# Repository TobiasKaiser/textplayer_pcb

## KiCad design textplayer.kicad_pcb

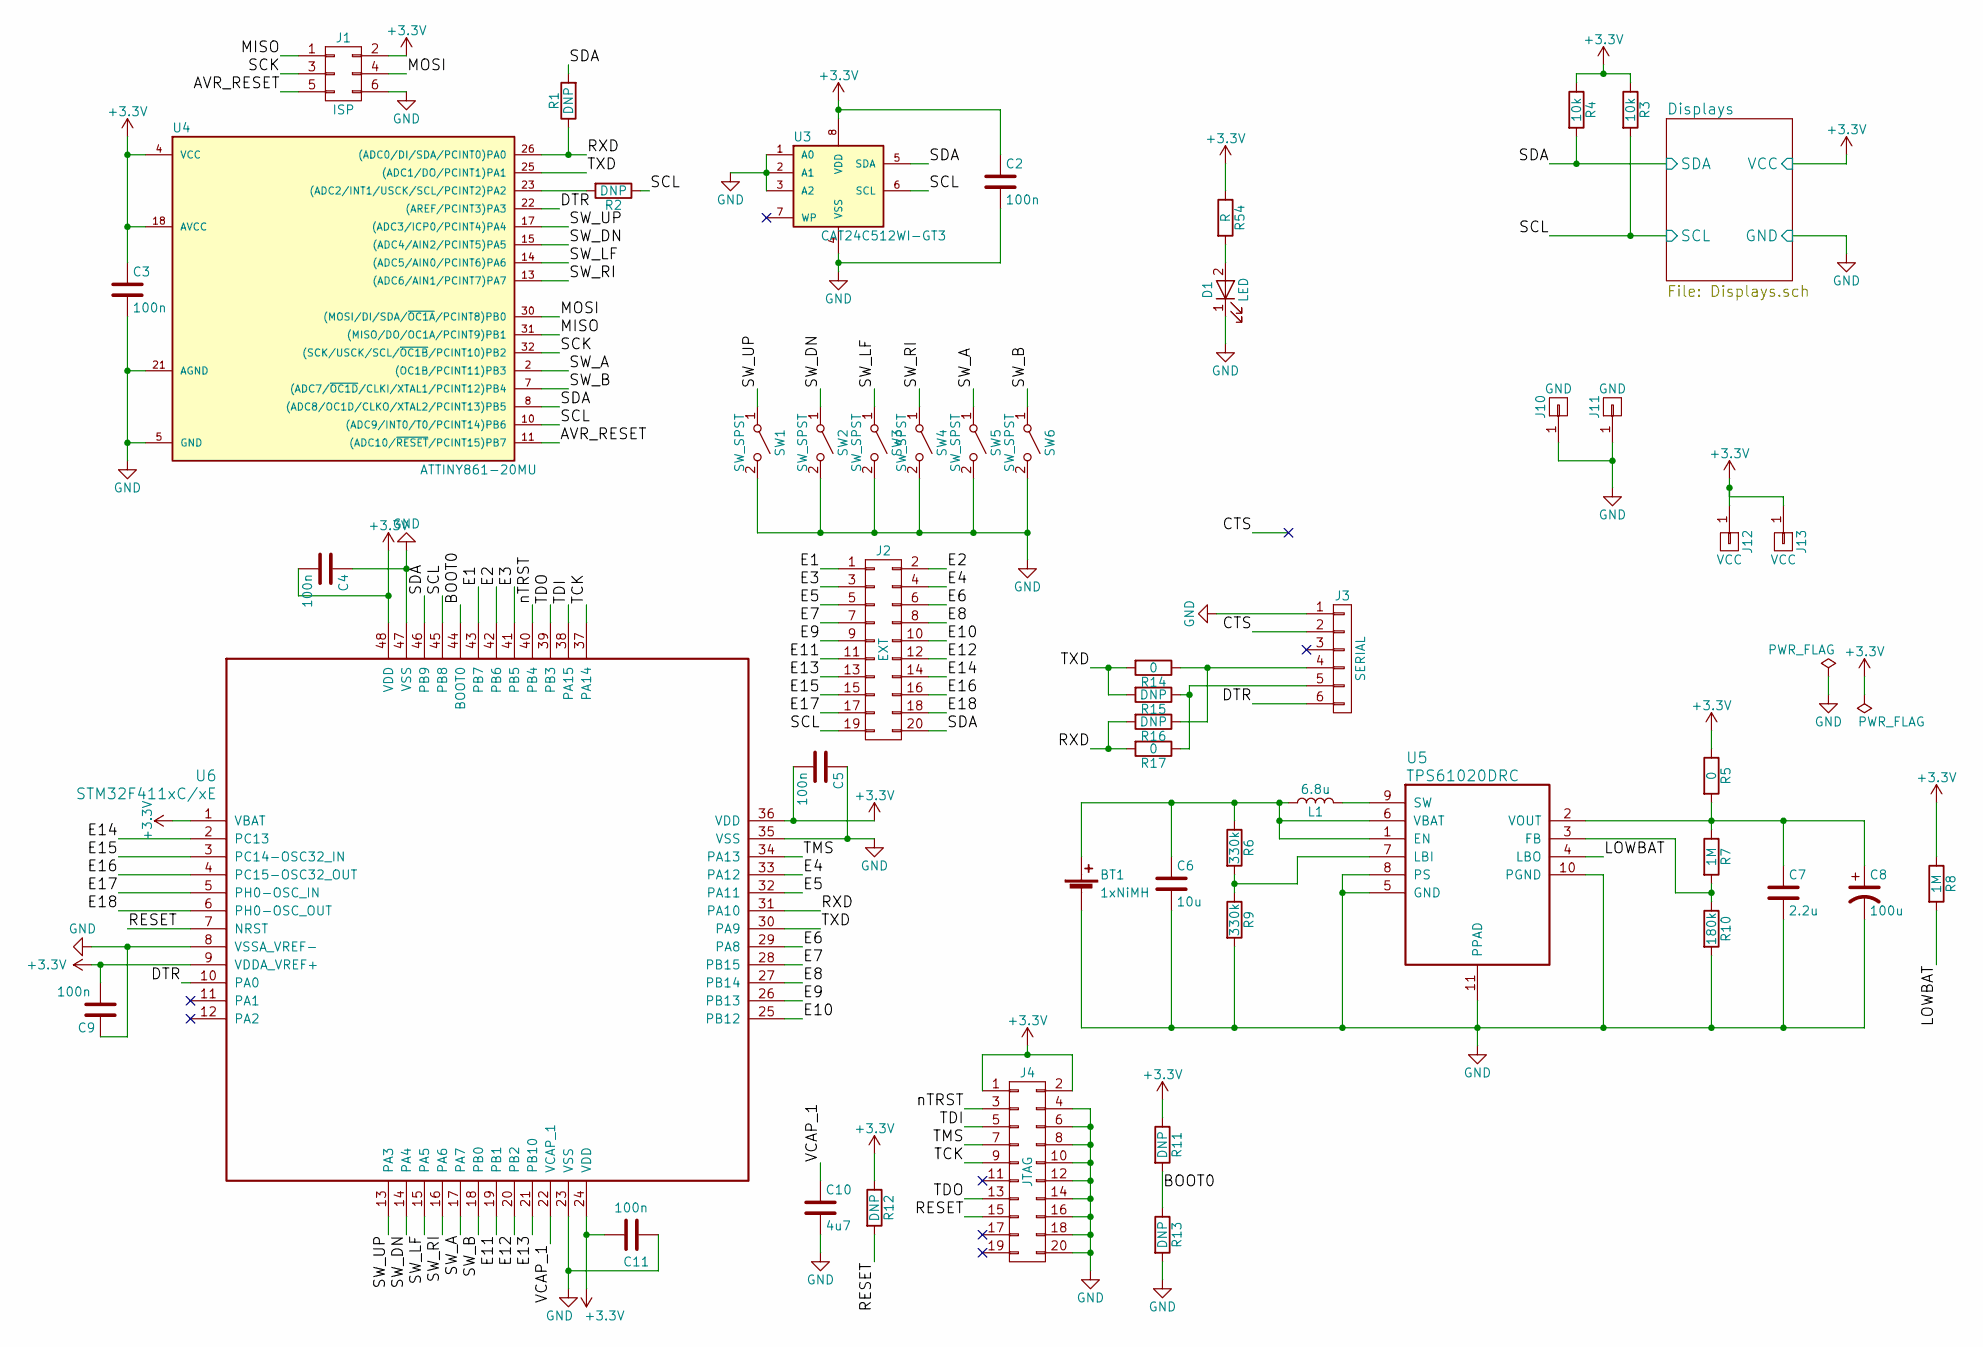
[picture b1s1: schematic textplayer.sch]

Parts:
BT1: 1xNiMH; BCAAPC
C2, C3, C4, C5, C9, C11: 100n; C_0805_HandSoldering
C6: 10u; C_0805_HandSoldering
C7: 2.2u; C_0805_HandSoldering
C8: 100u; CP_Tantalum_Case-B_EIA-3528-21_Hand
C10: 4u7; C_0805_HandSoldering
D1: LED; LED_0805
J1: ISP; Pin_Header_Straight_2x03_Pitch2.54mm
J2: EXT; Pin_Header_Straight_2x10_Pitch2.54mm
J3: SERIAL; Pin_Header_Straight_1x06_Pitch2.54mm
J4: JTAG; Pin_Header_Straight_2x10_Pitch2.54mm
J10: GND; Measurement_Point_Round-TH_Small
J11: GND; Measurement_Point_Round-SMD-Pad_Big
J12: VCC; Measurement_Point_Round-TH_Small
J13: VCC; Measurement_Point_Round-SMD-Pad_Big
L1: 6.8u; Inductor_B82462G4
R1, R2, R11, R12, R13, R15, R16: DNP; R_0805_HandSoldering
R3, R4: 10k; R_0805_HandSoldering
R5, R14, R17: 0; R_0805_HandSoldering
R6, R9: 330k; R_0805_HandSoldering
R7, R8: 1M; R_0805_HandSoldering
R10: 180k; R_0805_HandSoldering
R54: R; R_0805_HandSoldering
SW1, SW2, SW3, SW4, SW5, SW6: SW_SPST; SW_SPST_B3S-1000
U3: CAT24C512WI-GT3; TSSOP-8_4.4x3mm_Pitch0.65mm
U4: ATTINY861-20MU; QFN-32-1EP_5x5mm_Pitch0.5mm
U5: TPS61020DRC; S-PVSON-N10
U6: STM32F411xC/xE; QFN-48-1EP_7x7mm_Pitch0.5mm

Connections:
+3V3: C2.1, C3.1, C4.2, C5.2, C9.2, C11.2, J1.2, J4.1, J4.2, J12.1, J13.1, R3.1, R4.1, R5.1, R8.1, R11.1, R12.1, R54.1, U3.8 (VDD), U4.4 (VCC), U4.18 (AVCC), U6.1 (VBAT), U6.9 (VDDA_VREF+), U6.24 (VDD), U6.36 (VDD), U6.48 (VDD); also elsewhere on the board
/AVR_RESET: J1.5, U4.11 ((ADC10/~RESET~/PCINT15)PB7)
/BOOT0: R11.2, R13.1, U6.44 (BOOT0)
/CTS: J3.2
/DTR: J3.6, U4.22 ((AREF/PCINT3)PA3), U6.10 (PA0)
/E1: J2.1, U6.43 (PB7)
/E2: J2.2, U6.42 (PB6)
/E3: J2.3, U6.41 (PB5)
/E4: J2.4, U6.33 (PA12)
/E5: J2.5, U6.32 (PA11)
/E6: J2.6, U6.29 (PA8)
/E7: J2.7, U6.28 (PB15)
/E8: J2.8, U6.27 (PB14)
/E9: J2.9, U6.26 (PB13)
/E10: J2.10, U6.25 (PB12)
/E11: J2.11, U6.19 (PB1)
/E12: J2.12, U6.20 (PB2)
/E13: J2.13, U6.21 (PB10)
/E14: J2.14, U6.2 (PC13)
/E15: J2.15, U6.3 (PC14-OSC32_IN)
/E16: J2.16, U6.4 (PC15-OSC32_OUT)
/E17: J2.17, U6.5 (PH0-OSC_IN)
/E18: J2.18, U6.6 (PH0-OSC_OUT)
/LOWBAT: R8.2, U5.4 (LBO)
/MISO: J1.1, U4.31 ((MISO/DO/OC1A/PCINT9)PB1)
/MOSI: J1.4, U4.30 ((MOSI/DI/SDA/~OC1A~/PCINT8)PB0)
/RESET: J4.15, R12.2, U6.7 (NRST)
/RXD: R1.1, R16.2, R17.2, U4.26 ((ADC0/DI/SDA/PCINT0)PA0), U6.31 (PA10)
/SCK: J1.3, U4.32 ((SCK/USCK/SCL/~OC1B~/PCINT10)PB2)
/SCL: J2.19, R2.1, R3.2, U3.6 (SCL), U4.10 ((ADC9/INT0/T0/PCINT14)PB6), U6.45 (PB8); also elsewhere on the board
/SDA: J2.20, R1.2, R4.2, U3.5 (SDA), U4.8 ((ADC8/OC1D/CLKO/XTAL2/PCINT13)PB5), U6.46 (PB9); also elsewhere on the board
/SW_A: SW5.1 (A), U4.2 ((OC1B/PCINT11)PB3), U6.17 (PA7)
/SW_B: SW6.1 (A), U4.7 ((ADC7/~OC1D~/CLKI/XTAL1/PCINT12)PB4), U6.18 (PB0)
/SW_DN: SW2.1 (A), U4.15 ((ADC4/AIN2/PCINT5)PA5), U6.14 (PA4)
/SW_LF: SW3.1 (A), U4.14 ((ADC5/AIN0/PCINT6)PA6), U6.15 (PA5)
/SW_RI: SW4.1 (A), U4.13 ((ADC6/AIN1/PCINT7)PA7), U6.16 (PA6)
/SW_UP: SW1.1 (A), U4.17 ((ADC3/ICP0/PCINT4)PA4), U6.13 (PA3)
/TCK: J4.9, U6.37 (PA14)
/TDI: J4.5, U6.38 (PA15)
/TDO: J4.13, U6.39 (PB3)
/TMS: J4.7, U6.34 (PA13)
/TXD: R14.2, R15.2, U4.25 ((ADC1/DO/PCINT1)PA1), U6.30 (PA9)
/VCAP_1: C10.1, U6.22 (VCAP_1)
/nTRST: J4.3, U6.40 (PB4)
GND: BT1.2 (-), C2.2, C3.2, C4.1, C5.1, C6.2, C7.2, C8.2, C9.1, C10.2, C11.1, D1.1 (K), J1.6, J3.1, J4.4, J4.6, J4.8, J4.10, J4.12, J4.14, J4.16, J4.18, J4.20, J10.1, J11.1, R9.2, R10.2, R13.2, SW1.2 (B), SW2.2 (B), SW3.2 (B), SW4.2 (B), SW5.2 (B), SW6.2 (B), U3.1 (A0), U3.2 (A1), U3.3 (A2), U3.4 (VSS), U4.5 (GND), U4.21 (AGND), U5.5 (GND), U5.8 (PS), U5.10 (PGND), U5.11 (PPAD), U6.8 (VSSA_VREF-), U6.23 (VSS), U6.35 (VSS), U6.47 (VSS); also elsewhere on the board
unnamed: BT1.1 (+), C6.1, L1.1, R6.1, U5.1 (EN), U5.6 (VBAT)
unnamed: C7.1, C8.1, R5.2, R7.1, U5.2 (VOUT)
unnamed: D1.2 (A), R54.2
unnamed: J3.4, R14.1, R16.1
unnamed: J3.5, R15.1, R17.1
unnamed: L1.2, U5.9 (SW)
unnamed: R2.2, U4.23 ((ADC2/INT1/USCK/SCL/PCINT2)PA2)
unnamed: R6.2, R9.1, U5.7 (LBI)
unnamed: R7.2, R10.1, U5.3 (FB)

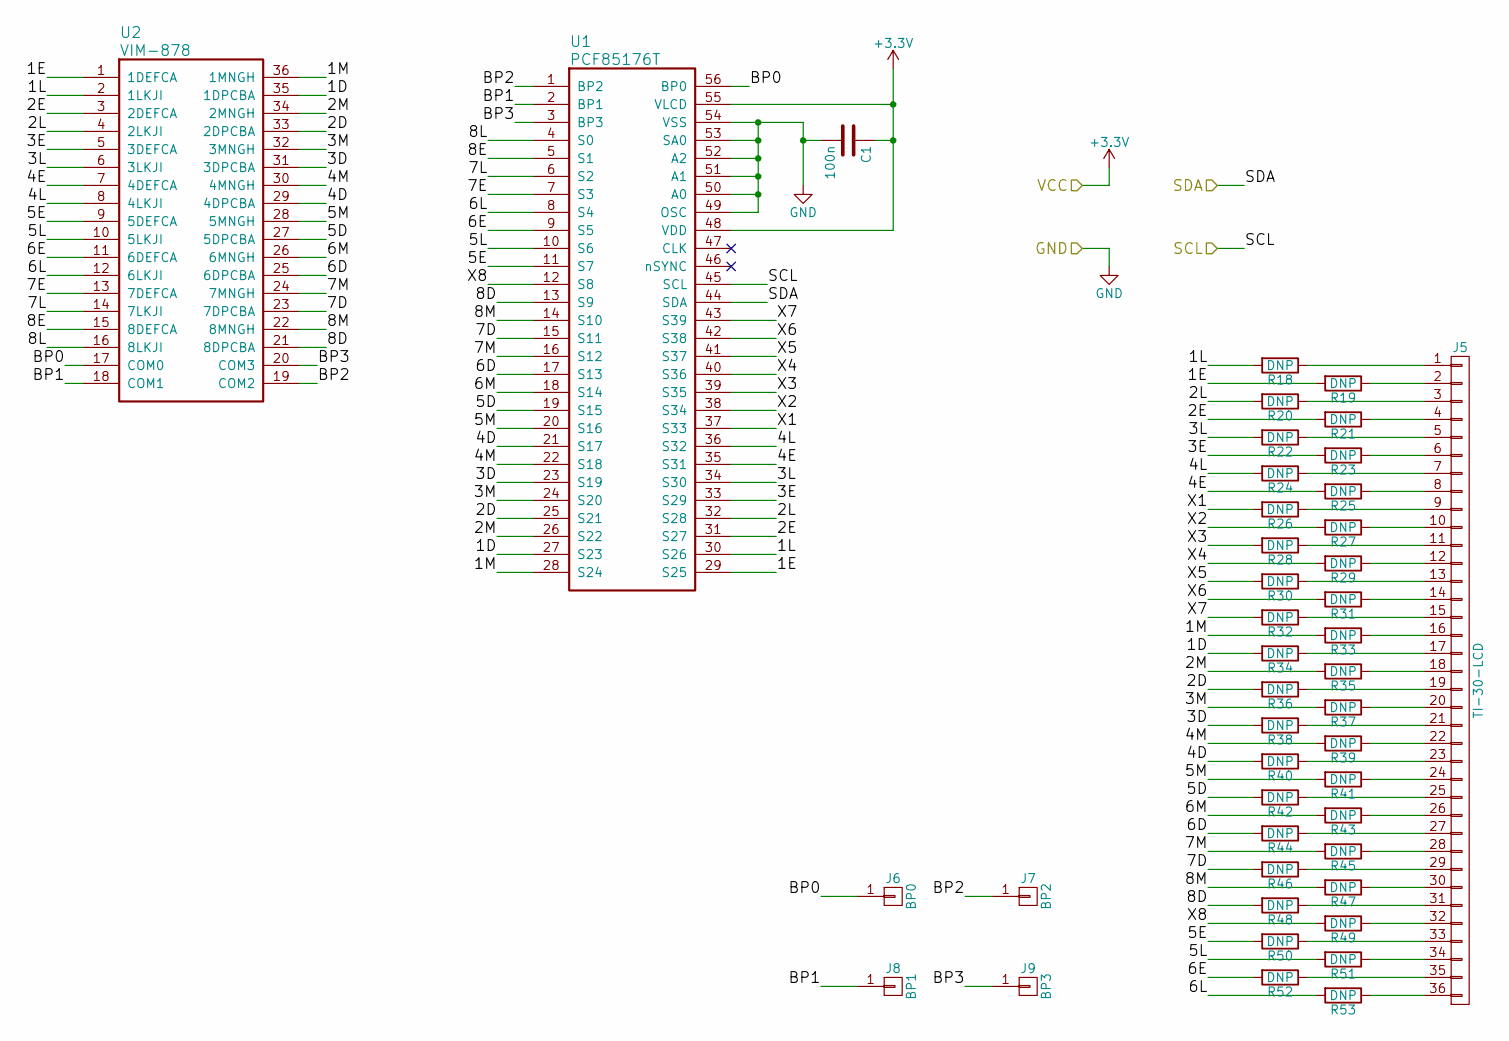
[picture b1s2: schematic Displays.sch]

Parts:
C1: 100n; C_0805_HandSoldering
J5: TI-30-LCD
J6: BP0; Measurement_Point_Square-SMD-Pad_Small
J7: BP2; Measurement_Point_Square-SMD-Pad_Small
J8: BP1; Measurement_Point_Square-SMD-Pad_Small
J9: BP3; Measurement_Point_Square-SMD-Pad_Small
R18, R19, R20, R21, R22, R23, R24, R25, R26, R27, R28, R29, R30, R31, R32, R33, R34, R35, R36, R37, R38, R39, R40, R41, R42, R43, R44, R45, R46, R47, R48, R49, R50, R51, R52, R53: DNP; R_0805_HandSoldering
U1: PCF85176T; TSSOP-56_6.1x14mm_Pitch0.5mm
U2: VIM-878

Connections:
+3V3: C1.1, U1.48 (VDD), U1.55 (VLCD); also elsewhere on the board
/Displays/1D: R34.2, U1.27 (S23), U2.35 (1DPCBA)
/Displays/1E: R19.2, U1.29 (S25), U2.1 (1DEFCA)
/Displays/1L: R18.2, U1.30 (S26), U2.2 (1LKJI)
/Displays/1M: R33.2, U1.28 (S24), U2.36 (1MNGH)
/Displays/2D: R36.2, U1.25 (S21), U2.33 (2DPCBA)
/Displays/2E: R21.2, U1.31 (S27), U2.3 (2DEFCA)
/Displays/2L: R20.2, U1.32 (S28), U2.4 (2LKJI)
/Displays/2M: R35.2, U1.26 (S22), U2.34 (2MNGH)
/Displays/3D: R38.2, U1.23 (S19), U2.31 (3DPCBA)
/Displays/3E: R23.2, U1.33 (S29), U2.5 (3DEFCA)
/Displays/3L: R22.2, U1.34 (S30), U2.6 (3LKJI)
/Displays/3M: R37.2, U1.24 (S20), U2.32 (3MNGH)
/Displays/4D: R40.2, U1.21 (S17), U2.29 (4DPCBA)
/Displays/4E: R25.2, U1.35 (S31), U2.7 (4DEFCA)
/Displays/4L: R24.2, U1.36 (S32), U2.8 (4LKJI)
/Displays/4M: R39.2, U1.22 (S18), U2.30 (4MNGH)
/Displays/5D: R42.2, U1.19 (S15), U2.27 (5DPCBA)
/Displays/5E: R50.2, U1.11 (S7), U2.9 (5DEFCA)
/Displays/5L: R51.2, U1.10 (S6), U2.10 (5LKJI)
/Displays/5M: R41.2, U1.20 (S16), U2.28 (5MNGH)
/Displays/6D: R44.2, U1.17 (S13), U2.25 (6DPCBA)
/Displays/6E: R52.2, U1.9 (S5), U2.11 (6DEFCA)
/Displays/6L: R53.2, U1.8 (S4), U2.12 (6LKJI)
/Displays/6M: R43.2, U1.18 (S14), U2.26 (6MNGH)
/Displays/7D: R46.2, U1.15 (S11), U2.23 (7DPCBA)
/Displays/7E: U1.7 (S3), U2.13 (7DEFCA)
/Displays/7L: U1.6 (S2), U2.14 (7LKJI)
/Displays/7M: R45.2, U1.16 (S12), U2.24 (7MNGH)
/Displays/8D: R48.2, U1.13 (S9), U2.21 (8DPCBA)
/Displays/8E: U1.5 (S1), U2.15 (8DEFCA)
/Displays/8L: U1.4 (S0), U2.16 (8LKJI)
/Displays/8M: R47.2, U1.14 (S10), U2.22 (8MNGH)
/Displays/BP0: J6.1, U1.56 (BP0), U2.17 (COM0)
/Displays/BP1: J8.1, U1.2 (BP1), U2.18 (COM1)
/Displays/BP2: J7.1, U1.1 (BP2), U2.19 (COM2)
/Displays/BP3: J9.1, U1.3 (BP3), U2.20 (COM3)
/Displays/X1: R26.2, U1.37 (S33)
/Displays/X2: R27.2, U1.38 (S34)
/Displays/X3: R28.2, U1.39 (S35)
/Displays/X4: R29.2, U1.40 (S36)
/Displays/X5: R30.2, U1.41 (S37)
/Displays/X6: R31.2, U1.42 (S38)
/Displays/X7: R32.2, U1.43 (S39)
/Displays/X8: R49.2, U1.12 (S8)
/SCL: U1.45 (SCL); also elsewhere on the board
/SDA: U1.44 (SDA); also elsewhere on the board
GND: C1.2, U1.49 (OSC), U1.50 (A0), U1.51 (A1), U1.52 (A2), U1.53 (SA0), U1.54 (VSS); also elsewhere on the board
unnamed: J5.1, R18.1
unnamed: J5.2, R19.1
unnamed: J5.3, R20.1
unnamed: J5.4, R21.1
unnamed: J5.5, R22.1
unnamed: J5.6, R23.1
unnamed: J5.7, R24.1
unnamed: J5.8, R25.1
unnamed: J5.9, R26.1
unnamed: J5.10, R27.1
unnamed: J5.11, R28.1
unnamed: J5.12, R29.1
unnamed: J5.13, R30.1
unnamed: J5.14, R31.1
unnamed: J5.15, R32.1
unnamed: J5.16, R33.1
unnamed: J5.17, R34.1
unnamed: J5.18, R35.1
unnamed: J5.19, R36.1
unnamed: J5.20, R37.1
unnamed: J5.21, R38.1
unnamed: J5.22, R39.1
unnamed: J5.23, R40.1
unnamed: J5.24, R41.1
unnamed: J5.25, R42.1
unnamed: J5.26, R43.1
unnamed: J5.27, R44.1
unnamed: J5.28, R45.1
unnamed: J5.29, R46.1
unnamed: J5.30, R47.1
unnamed: J5.31, R48.1
unnamed: J5.32, R49.1
unnamed: J5.33, R50.1
unnamed: J5.34, R51.1
unnamed: J5.35, R52.1
unnamed: J5.36, R53.1

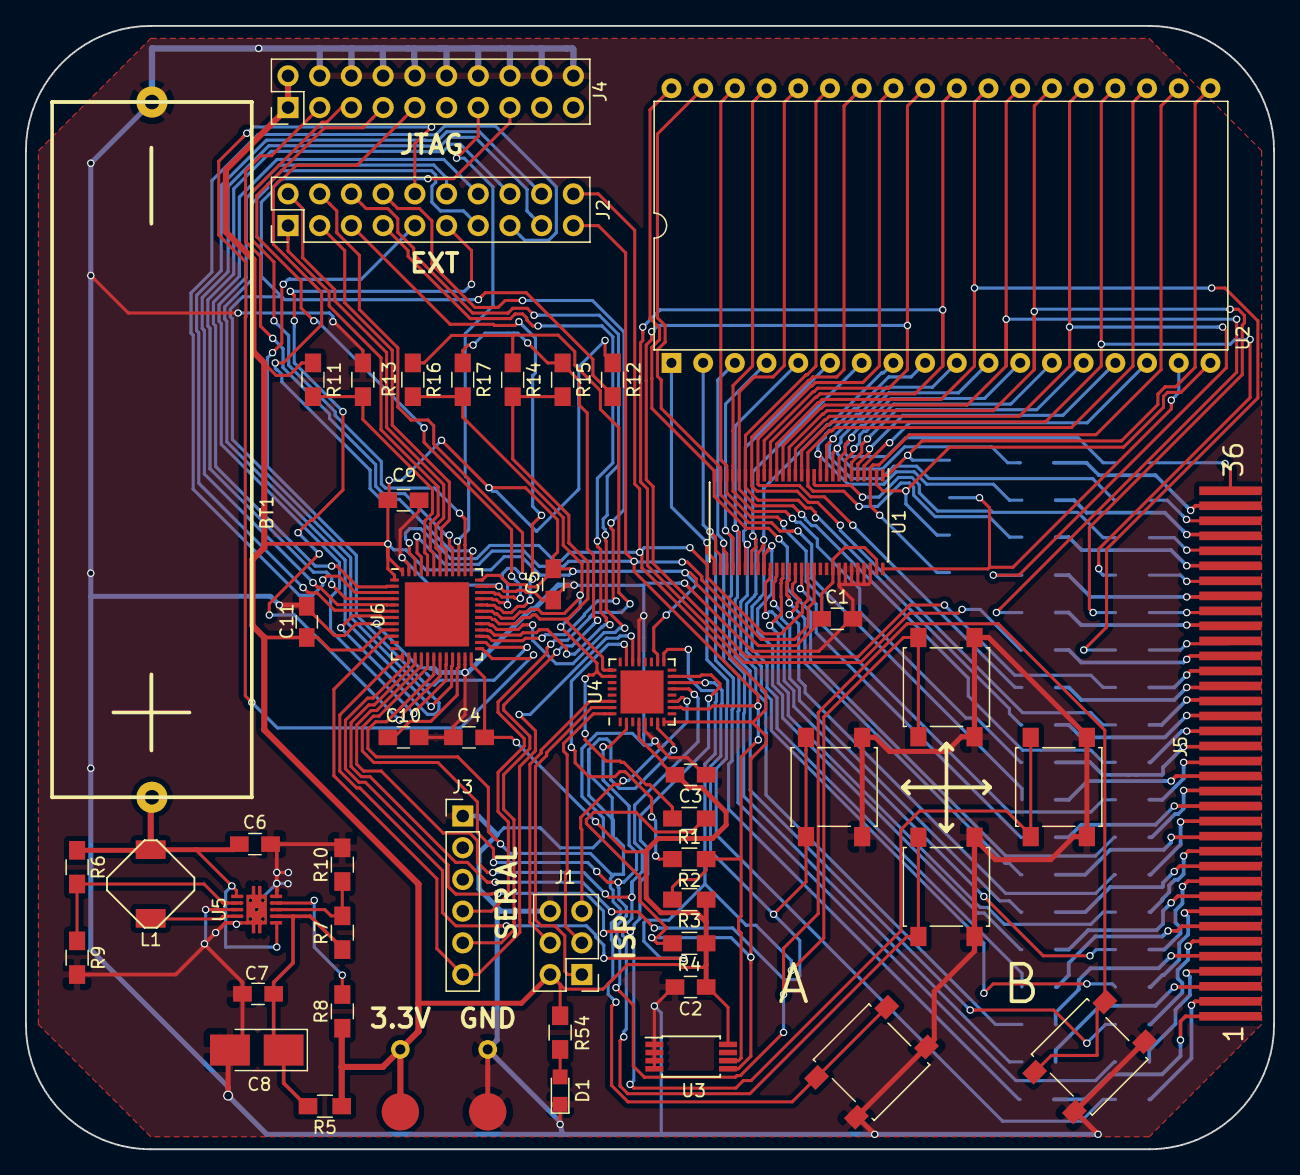
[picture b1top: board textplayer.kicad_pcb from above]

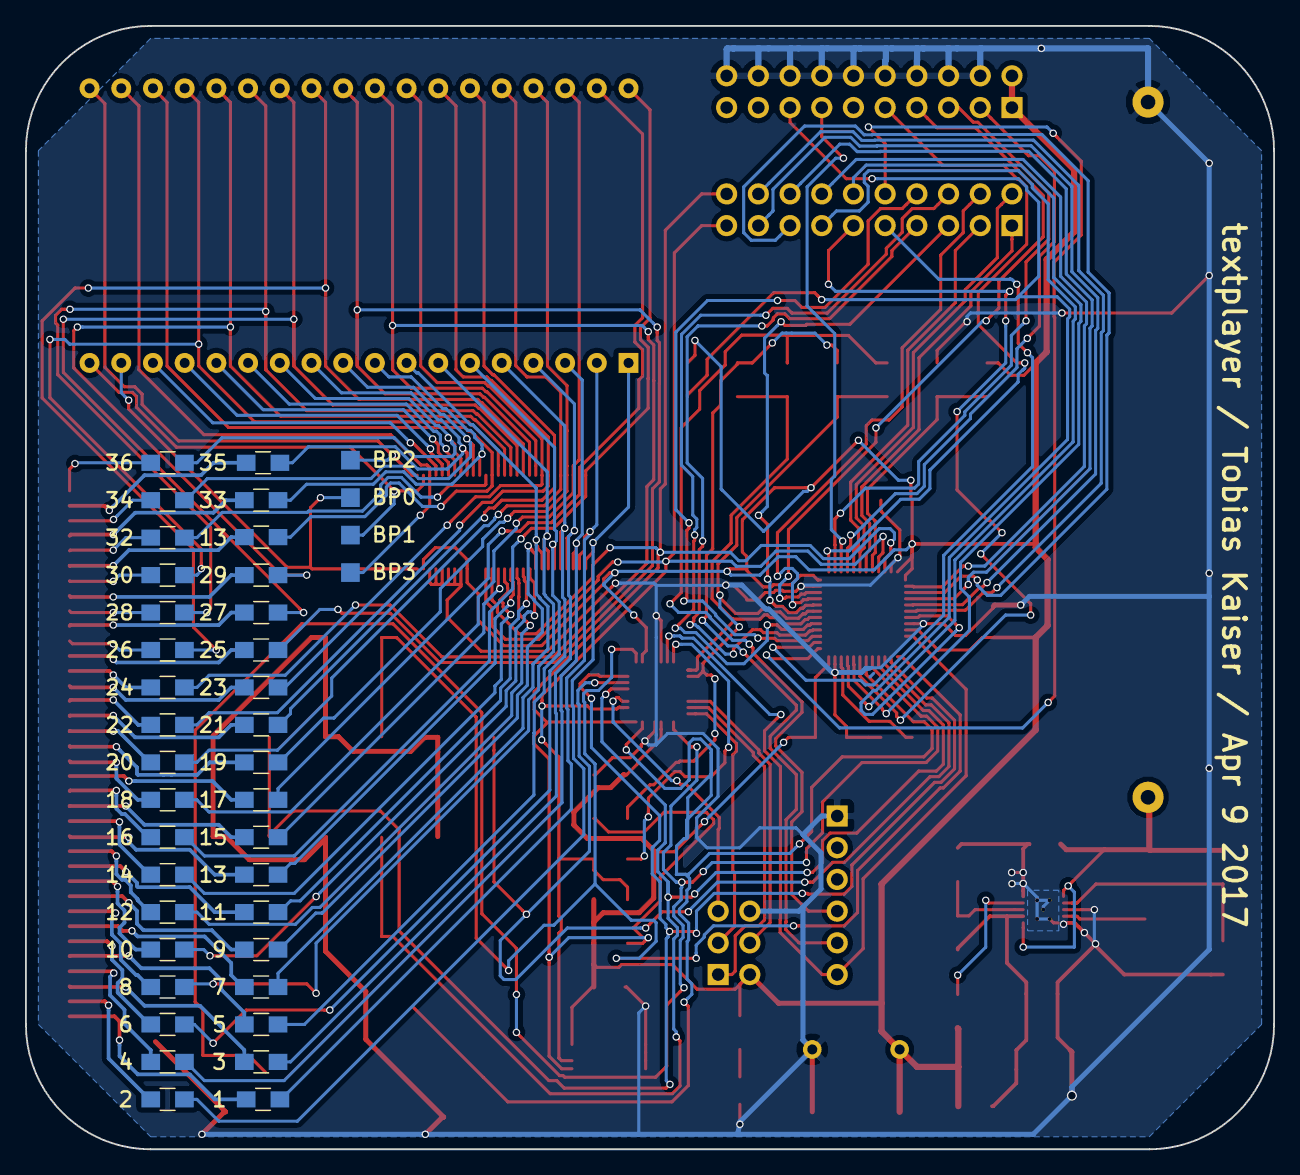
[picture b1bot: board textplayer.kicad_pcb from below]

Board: 2 copper layers, 100.0 x 90.0 mm, 93 parts (40 on the bottom side), 133 nets.

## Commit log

2017-04-08 schematic almost done
2017-04-08 first pcb attempts
2017-04-08 placing...
2017-04-09 displays schematic ausgelagert
2017-04-09 place should be done now
2017-04-09 routing...
2017-04-09 more routing...
2017-04-09 5 unconnected
2017-04-09 almost done..
2017-04-09 werde es jetzt gleich absenden
2017-04-11 first pcb ordered on Apr 10 2017
